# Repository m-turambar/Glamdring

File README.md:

# Glamdring
Infraestructura para microcontroladores STM32.
Desarrollo de hardware: STM32G031

El proyecto en usa una capa de abstracción del hardware (HAL) original.

Periféricos:
* MPU6050
* NRF24

Desarrollo de hardware para:
* STM32G031

El proyecto Glamdring es un éxito.

**************************************************
Dependencias:
* Compilador ARM-none-eabi. https://developer.arm.com/downloads/-/gnu-rm
* Flasher OpenOCD: https://openocd.org/pages/getting-openocd.html
* Drivers de ST. https://www.st.com/en/development-tools/stsw-link009.html

**************************************************

https://www.youtube.com/watch?v=ew0XWd-blwE&t=2509s

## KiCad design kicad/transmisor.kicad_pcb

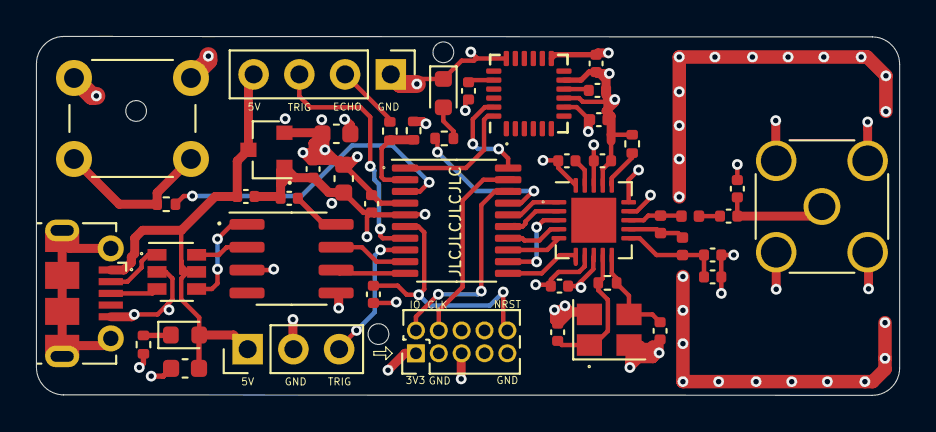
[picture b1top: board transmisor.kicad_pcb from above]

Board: 4 copper layers, 48.0 x 19.9 mm, 46 parts (0 on the bottom side), 41 nets.

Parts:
AE1: Antenna_Shield; SMA_Wurth_60312002114503_Vertical
C1, C17: 10nF; C_0402_1005Metric
C2: 1nF; C_0402_1005Metric
C3: 33nF; C_0402_1005Metric
C4, C6: 22pF; C_0402_1005Metric
C5, C20: 2.2nF; C_0402_1005Metric
C7: 4.7pF; C_0402_1005Metric
C8: 1.5pF; C_0402_1005Metric
C9: 1.0pF; C_0402_1005Metric
C10: 10uF; C_0603_1608Metric
C11, C12, C14, C16, C18, C19, C21: 100nF; C_0402_1005Metric
C13: 4.7uF; C_0603_1608Metric
C15: 1uF; C_0603_1608Metric
D1: LED_g; LED_0603_1608Metric
D2: LED_w; LED_0603_1608Metric
J1: USB_B_Micro; USB_Micro-B_Molex-105017-0001
J2: Conn_02x05_Odd_Even; PinHeader_2x05_P1.27mm_Vertical
J3: Conn_01x03_Female; PinHeader_1x03_P2.54mm_Vertical
J4: Conn_01x04_Female; PinHeader_1x04_P2.54mm_Vertical
L1: 8.2nH; L_0402_1005Metric
L2: 3.9nH; L_0402_1005Metric
L3: 2.7nH; L_0402_1005Metric
R1: 22k; R_0402_1005Metric
R2: 1M; R_0402_1005Metric
R3, R4, R6, R7, R8: 2.2k; R_0402_1005Metric
SW1: SW_Push_Dual; SW_PUSH_6mm_H9.5mm
U1: NRF24L01+; QFN-20-1EP_4x4mm_P0.5mm_EP2.5x2.5mm
U2: CH330N; SOIC-8_3.9x4.9mm_P1.27mm
U3: XC6206PxxxMR; SOT-23
U4: STM32G031F8Px; TSSOP-20_4.4x6.5mm_P0.65mm
U5: USBLC6-2SC6; SOT-23-6
U6: MPU-6050; InvenSense_QFN-24_4x4mm_P0.5mm
Y1: 16 MHz; Crystal_SMD_3225-4Pin_3.2x2.5mm

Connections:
5V: C10.1, C12.1, D1.2, J1.1, J3.1, J4.4, U3.3, U5.5
+3V3: C1.1, C2.1, C13.1, C14.1, C15.1, C16.1, C17.1, C18.1, J2.1, U1.7, U1.15, U1.18, U2.5, U3.2, U4.4, U6.8, U6.13
BOTON: R6.2, U4.3
GND: AE1.2, C1.2, C2.2, C3.2, C4.2, C5.2, C6.2, C7.2, C9.2, C10.2, C11.2, C12.2, C13.2, C14.2, C15.2, C16.2, C17.2, C18.2, C19.2, C20.2, C21.2, D2.1, J1.5, J2.3, J2.5, J2.9, J3.2, J4.1, R1.2, R3.2, R8.1, SW1.2, U1.8, U1.14, U1.17, U1.20, U2.3, U3.1, U4.5, U5.2, U6.9, U6.11, U6.18, Y1.2, Y1.4
I2C1_CLK: U4.20, U6.23
I2C1_SDA: U4.1, U6.24
LED1: R4.1, U4.17
NRF24_CE: U1.1, U4.16
NRF24_IRQ: U1.6, U4.11
NRST: C21.1, J2.10, U4.6
unnamed: AE1.1, C8.1, C9.1
unnamed: C3.1, U1.19
unnamed: C4.1, R2.2, U1.9, Y1.1
unnamed: C5.1, C7.1, L3.1, U1.11
unnamed: C6.1, R2.1, U1.10, Y1.3
unnamed: C8.2, L2.1
unnamed: C11.1, U2.8
unnamed: C19.1, U6.10
unnamed: C20.1, U6.20
unnamed: D1.1, R3.1
unnamed: D2.2, R4.2
unnamed: J1.2, U5.1
unnamed: J1.3, U5.3
unnamed: J4.2, R7.2
unnamed: L1.1, L3.2, U1.12
unnamed: L1.2, L2.2, U1.13
unnamed: R1.1, U1.16
unnamed: R6.1, SW1.1
unnamed: U2.1, U5.4
unnamed: U2.2, U5.6
RELAY_TRIG: J3.3, U4.8
SPI_CLK: U1.3, U4.12
SPI_CS: U1.2, U4.15
SPI_MISO: U1.5, U4.13
SPI_MOSI: U1.4, U4.14
SWD_CLK: J2.4, U4.19
SWD_IO: J2.2, U4.18
TIM2_CH1: J4.3, U4.7
TIM17_CH1: R7.1, R8.2, U4.2
UART2_RX: U2.6, U4.10
UART2_TX: U2.7, U4.9

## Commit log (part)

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2019-09-25 Genesis, some scribbling
2019-09-25 adding sample startup file
2019-09-25 Testing push
2019-10-21 -meh, systick interrupt and user button int enabled
2019-11-08 añadiendo codigo para el g0
2019-11-11 weekend work. not building yet
2019-11-11 wip, gitignore
2020-02-15 Added proper make clean, and most importantly, updated README.md with info to make the build system much better
2020-05-05 Stepper motor old code, forgot to commit it. Going to work on something else so I want to save the code somewhere
2020-05-10 cmake script not working on windows due to linking step
2020-05-18 Major modifications: Dropping CMake efforts due to linking error. Sticking to Makefile and compilation database to enable integration with Clion. Enabled C++ in Makefile. Developing a small i2c drive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
2020-05-27 Major breakthrough, managed to setup clion working perfectly for embedded development. I can debug, analyze registers using .svd files, build and flash the code using OCD. Developed a small driver fo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
2020-05-27 deleting old STM32G070 directory since it was fully bugged in clion
2020-06-05 refactored memory function to helpers.cpp, added thin write/read function to i2c class. Created placeholder from basic timer drivers
2020-06-05 beginning work on the basic timer
2020-06-07 Managed to get the interrupts of TIM6 working - What was failing: Linkage was not set to C in basic_timer.h, so linker was not finding the right interrupt handler. Work remains to make the interface 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
2020-06-10 Added bugfix to I2C driver - I2C1 was incorrectly initializing PORTB pin instead of A. Changed error types for main I2C functions. Added 25ms timeout to I2C code
2020-06-10 example of passing a user written callback as a callback for our timer interrupt, using a normal function, and a lambda that doesn't capture
2020-06-15 big commit, adding incomplete general purpose timer and gpio drivers. Working on them. GPT can do OPM and periodic interrupts just like basic timers
2020-06-15 Updating so that users know this is the right way of building the repo
2020-06-15 removing confusing unused makefile and cmake script
2020-06-15 Refined GPIO driver
2020-06-16 fixed bug in helpers.h where I wasn't performing a mask clear properly, gpio driver appears to work successfully, using it instead of HAL to configure I2C pins and everything works properly
2020-06-16 Some aesthethic changes, substituted stm32cube's gpio.c file for our new driver. About to develop either UART, PWR, or continue RCC drivers
2020-06-18 Saving work, I2C busy unresponsive, BUSY=1, reverting to last commit to see changes
2020-06-18 fixed GPIO initialization bug preventing I2C from operating correctly
2020-06-18 UART driver beta working, only supported UART so far is UART2. Tests successful
2020-06-20 enabled uart interrupt mechanism. Uart3 now able to forward data to Uart2 through interrupts. I was getting a strange corruption when done by polling, possibly due to tx_buf overflowing. Increased si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
2020-06-20 deleting old stm32 hal based uart file, since we now have our own driver working. Forgot last commit to add startup file since we did do a couple changes there to enable the uart interrupts
2020-08-08 reestructurando
2020-12-06 Finally some work. Added PWR namespace, with ability to configure regulator. Restructured bitfield class and added member functions to register class
2020-12-08 Agregaste módulos del RCC para inicialización de los relojes de los buses APB, AHB; gran commit lleno de cambios buenos a los drivers
2020-12-10 Libre de HAL de ST. Todavia usas ASM code, pero ya ningún driver de ellos
2021-02-02 haciendo algunos cambios, agregando el código del NRF24, y prototipos de los otros micros
2021-02-02 idea interesante
2021-02-05 Intento de desvincular la HAL de cada micro
2021-02-05 UART funcional en M7. Duplicando ultimo caracter. Estructura del código se siente bien
2021-02-07 Reestructuración exitosa. One HAL to rule them all. Lol. Comunicación usando el NRF2401 entre el M0+ y el M7 usando interrupciones de un timer y polling del NRF es todo un exito. Falta hacer pruebas 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
2021-02-07 ignorar
2021-03-13 quitando los gpio_af específicos, pues hay demasiada variedad.
2021-06-28 Agregando interfaz más usable para PWM, así como una prueba que permite a través del uart configurar los registros de un timer, para poderlo probar y poner a diferentes frecuencias y anchos de pulso
2021-07-06 dustoff
2021-07-09 por fin entendiste el prescaler y el ARR
2021-07-10 Arregle el bug OPM interrupcion inmediata.... :)
2021-07-13 Input Capture interrupciones bien, conteo mal
2021-07-13 Input capture funciona de maravilla. Midiendo pulsos de 4 o 7 milisegundos con plena exactitud.
2021-07-30 G031 hola led
2021-07-31 G031 funcionando con timer general y uart. uart no tiene fifo, como consecuencia causaba errores. Arreglado
2021-08-03 I2C con acelerometro funciona perfecto
2021-08-13 NRF24 funcionando con interrupciones. Excelente funcionamiento. Agregaste caso para interrupcion en UART cuando ORE se setea.
2021-08-13 Ahora sí resolviste el problema de la UART. También arreglaste bug the MAX_RT en el NRF. funciona perfecto. Llega al jardín pero no al motor
2021-08-15 transceptor 0.1
2021-08-23 transmisor 0.1
2021-10-23 Agregando cambios viejos
2021-10-25 Moviendo lambdas a funciones. Actualizando README. Funcion para prender/apagar rele. Parsing ocurre a datos recibidos por nrf_rx tambien, ademas de UART2.
2021-11-14 Blind commit - last attempts were to fix I2C blocking issues when powering on without debugger
2021-11-14 fix de incompatibilidad de tim2 con micros que no lo tienen. Hecho con las nalgas. Los ultimos commits han estado hechos con las nalgas
2021-11-15 Driver Powerstep
2021-12-28 Agregando los ultimos cambios que quedaron pendientes cuando trabajabas con el motor a pasos.
2021-12-30 Refactor los archivos de aplicacion a sus respectivos archivos, agregue un time OPM para apagar el relevador
2022-01-02 Agregaste apagar() a NRF24. Agregaste función para descartar TX fifo en la aplicación del NRF24. Agregaste manera de alternar en runtime entre TX y RX para el NRF24. Arreglaste bug en rutina que obti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
2022-02-13 Agregaste capacidad de enviar mensajes en otros canales. RX_ADDR_P0 debe ser igual a TX_ADDR para recibir ACK. Modificaste data rate a 250Kb/s. Agregaste comandos para poder ver el estado del buffer 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
2022-08-20 wip pendiente del f767
2022-08-20 Mejoraste la interfaz PWM. Agregaste la capacidad de habilitar salida de varios canales.
2022-08-20 R - basic timer
2022-12-03 agregaste capacidad de cambiar frecuencia de TIM2 en runtime
2022-12-11 leftovers
2022-12-13 Agregaste lectura de temperatura del MPU6050
2022-12-15 Rename HAL header guards to be GLAMDRING*
2022-12-17 Make registro ctor explicit.
2022-12-17 Address static code analysis warnings
2025-04-11 Major update. GUI intro. Minimal build scripts. F767 PWM and UART.
2025-04-12 DAC 1.0
2025-06-24 R - CMake refactor
2025-06-24 Fix gitignore of toolchain.cmake
2025-06-25 Refactor build path, scripts, etc. Delete old obsolete files
2025-06-25 Actualización de notas
2025-09-16 R - mainly substitute include guards
2025-09-16 R - header guards
2025-09-16 mover definiciones
2025-09-16 mv Buffer
2025-09-17 Procesador
2025-09-17 mv app
2025-09-17 Parece estable. Relays funcionando
2025-09-17 Fix previous commits OPM issue. Added callback_data to general_timer
2025-09-18 Reestructura de app_rele a app_gpio
2025-09-18 wip - primera prueba echo con python
2025-09-19 Forbid basic_timer in G031. And fix G031 vector table.
2025-09-19 Fix OPM bug general_timer
2025-09-21 Procesador puede anidar mensajes e.g. {n/{gt}}
2025-10-25 unrevised - last state
2025-11-15 Cambios UART1 para que Dongle funcione
2025-11-22 Modificar API SPI - 1.0 escribir es leer
2026-06-25 R - pequenios cambios a NRF24
2026-06-25 R - formato torpe
2026-06-25 Cambios opcionales para puentear dos UART
2026-06-25 Add CLAUDE.md
2026-06-25 Clang format
2026-06-30 Add system reset to Procesador
